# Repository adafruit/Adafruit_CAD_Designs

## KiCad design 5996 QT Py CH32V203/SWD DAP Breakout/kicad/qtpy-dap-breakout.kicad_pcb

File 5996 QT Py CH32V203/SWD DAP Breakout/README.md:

# QT Py CH32V203 SWD DAP Breakout

A 40 x 42 mm carrier that turns an Adafruit QT Py CH32V203 into a debug probe. The silk title is "WCH + ARM Programmer". It works two ways:

| Mode | Targets |
|---|---|
| WCH SWIO programmer | Metro CH32V407 and CH32V467 |
| ARM SWD CMSIS-DAP probe | ARM Cortex targets on the 10-pin header |

No pull-up resistor is needed on SWIO. The SWIO firmware is in [Adafruit_DAP PR #60](https://github.com/adafruit/Adafruit_DAP/pull/60).

The QT Py plugs into the inner rows of two 2x7 SMD sockets. The outer rows repeat every QT Py pin, so you can plug jumper wires in for the spare IO, like the Proto Doubler PiCowbell. A 2x5 1.27 mm box header takes a 1675 cable to the target. It is a single-sided board made to be cut at home on a laser or a mill: no vias, a GND pour, 45 degree bends only.

## Files

| File | What |
|---|---|
| [5996 QT Py CH32V203 SWD DAP Breakout.stpZ](5996%20QT%20Py%20CH32V203%20SWD%20DAP%20Breakout.stpZ) | Board with QT Py, sockets and box header, gzipped STEP |
| [kicad/qtpy-dap-breakout.kicad_pcb](kicad/qtpy-dap-breakout.kicad_pcb) | KiCad 10 board |
| [kicad/qtpy-dap-breakout.kicad_pro](kicad/qtpy-dap-breakout.kicad_pro) | KiCad 10 project |
| [kicad/build_pcb.py](kicad/build_pcb.py) | Regenerates the board from scratch |
| [kicad/fp-lib-table](kicad/fp-lib-table) | Points KiCad at `models/QTPyDAP.pretty` |
| [models/QTPyDAP.pretty](models/QTPyDAP.pretty) | 752 box header footprint |
| [models/BoxHeader_2x05_P1.27mm_SMD_752.step](models/BoxHeader_2x05_P1.27mm_SMD_752.step) | 752 box header STEP |
| [models/QTPy_CH32V203_5996.stpZ](models/QTPy_CH32V203_5996.stpZ) | QT Py CH32V203 model, gzipped STEP |
| [models/gen_box_header_752.py](models/gen_box_header_752.py) | Generates the box header model |
| [milling/qtpy-dap-breakout-F_Cu.gbr](milling/qtpy-dap-breakout-F_Cu.gbr) | F.Cu Gerber |
| [milling/qtpy-dap-breakout-Edge_Cuts.gbr](milling/qtpy-dap-breakout-Edge_Cuts.gbr) | Edge.Cuts Gerber |
| [milling/qtpy-dap-breakout.drl](milling/qtpy-dap-breakout.drl) | Drill file |
| [milling/qtpy-dap-breakout-job.gbrjob](milling/qtpy-dap-breakout-job.gbrjob) | Gerber job file |
| [milling/F_Cu-reference.pdf](milling/F_Cu-reference.pdf) | 1:1 etch PDF |
| [milling/F_Cu-mirrored-1to1.pdf](milling/F_Cu-mirrored-1to1.pdf) | 1:1 etch PDF, mirrored |

A SKADIS mount for this board, with its STEP, 3MF and FreeCAD files, is in [SKADIS Mount](../SWD%20DAP%20Breakout%20SKADIS%20Mount).

## Parts

| Ref | Part | Qty |
|---|---|---|
| U1 | Adafruit QT Py CH32V203 (PID 5996) | 1 |
| J1, J2 | 2x7 2.54 mm SMD female socket, cut from an Adafruit 2187 2x20 short SMT socket, one per QT Py side | 2 |
| J3 | Adafruit 752 2x5 1.27 mm SMT box header, 10-pin ARM Cortex | 1 |
| J4, J5 | 1x7 2.54 mm male header strip, solders to the QT Py | 2 |
| | Adafruit 1675 SWD cable, 2x5 1.27 mm, 150 mm | 1 |
| | M2 x 4 screw, into the SKADIS mount's heat set inserts | 4 |
| | Single-sided copper-clad blank, 40 x 42 mm | 1 |

## Pinout

| Header J3 | Signal | QT Py | Metro CH32V407/467 (JDEBUG) |
|---|---|---|---|
| 1 | VTref | not connected | 1, the Metro's own 3.3 V |
| 2 | SWDIO / SWIO | A3 | 2 (PA13) |
| 3, 5, 9 | GND | GND | 3, 5, 9 |
| 4 | SWCLK | A2 | 4 (PA14, unused in SWIO mode) |
| 6, 7, 8 | not connected | | |
| 10 | nRESET | A0 | 10 |

- Only 3.3 V targets. There is no level shifting.
- The breakout does not power the target, like the Raspberry Pi Debug Probe. The target needs its own supply. Pin 1 is left open so the Metro's 3.3 V never meets the QT Py's.
- The UART is not wired to the box header. TX and RX, like every other QT Py pin, are on the outer socket rows.
- Each QT Py pin has a second socket on the outer row, labeled on the silk. The two contacts of each pin are tied by a trace under the socket.

## Firmware

Liz Clark's Adafruit_DAP examples run as-is with this wiring.

| Example | Result |
|---|---|
| `ch32_host/cmsis_dap_probe` | Runs as-is. Its UART bridge is on the QT Py TX and RX pins, reachable on the outer socket rows |
| `ch32_host/dragdrop_programmer` | Runs as-is |
| `stm32/stm32f4_test` | Runs as-is |

Most other examples do not fit this board:

| Group | Examples | Why |
|---|---|---|
| Needs pin changes | `samd21/flash_MKR_bootloaders`, `samd51/samx5_flash_from_header`, `nrf/nrf52_test` | Pins are hardcoded. The samx5 image may not fit in flash |
| Needs SD card, SPI flash or WiFi | `samd21/flash_from_SD`, `samd21/flash_from_SPI_flash`, `samd21/SWD_standalone_core`, `stm32/stm32_flash_from_SD`, `nrf/flash_feather52`, `nrf/flash_feather52840`, `nrf/flash_nrf51_from_SPI_flash`, `ESPHost/*` | The breakout has none of these |
| Image too large | `samd21/flash_from_header` | 239 KB image, more than 7 times the 32 KB flash |

Tested through the breakout:

| Target | Firmware | Result |
|---|---|---|
| Metro CH32V407 | [Adafruit_DAP PR #60](https://github.com/adafruit/Adafruit_DAP/pull/60) | Programmed and verified in 66.5 s |
| Metro CH32V467 | [Adafruit_DAP PR #60](https://github.com/adafruit/Adafruit_DAP/pull/60) | Programmed and verified TinyUF2 in 67.0 s, chip ID 10/10 |
| Metro M0 Express (SAMD21G18A) | `ch32_host/cmsis_dap_probe` | Read over SWD with OpenOCD at 400 kHz |

## Milling

Cut on F.Cu only. Signal traces are 0.76 mm with 45 degree miters. GND is a pour with 0.5 mm clearance and solid pad connections, with no GND traces. The tightest gap is 0.51 mm between the box header pads. A fiber laser such as the xTool F1 Ultra handles it; a mill needs a 0.4 mm end mill or a fine V-bit.

The Metro and QT Py in the renders are approximate models, not official CAD.

In the Data 70 font, D reads like O ("SWD", "GND") and 1 reads like I in the date.

## Credits

Probe firmware by Liz Clark (Adafruit_DAP, ch32_host examples). The QT Py model is built from Liz's [QT Py CH32V203 Eagle board](https://github.com/adafruit/Adafruit-QT-Py-CH32V203-PCB).

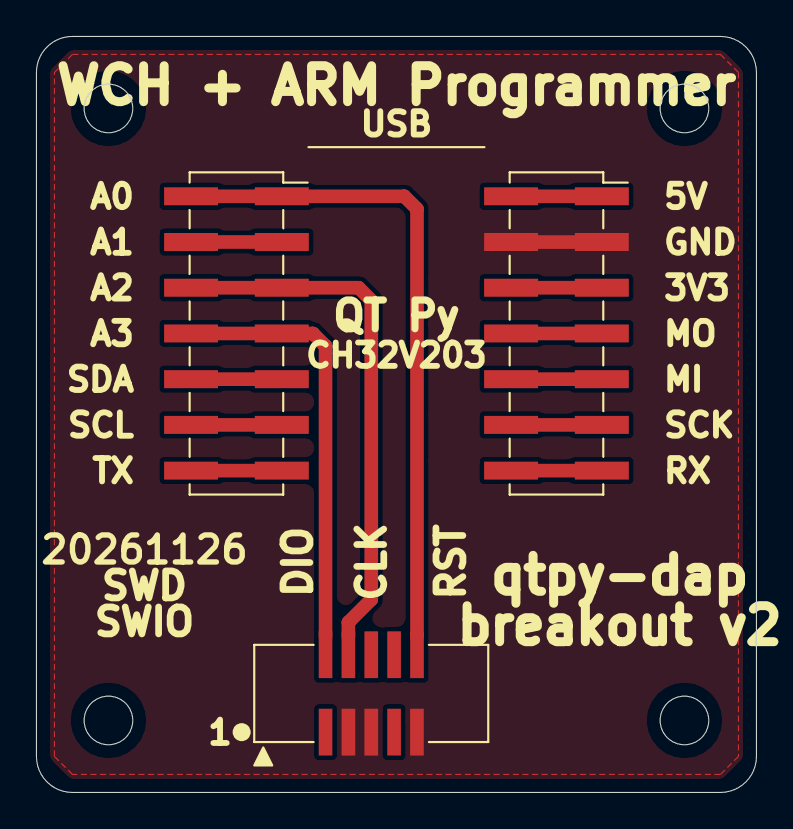
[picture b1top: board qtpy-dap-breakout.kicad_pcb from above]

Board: 2 copper layers, 40.0 x 42.0 mm, 4 parts (0 on the bottom side), 14 nets.

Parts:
J1: QT Py left (2187 cut 2x7); PinSocket_2x07_P2.54mm_Vertical_SMD
J2: QT Py right (2187 cut 2x7); PinSocket_2x07_P2.54mm_Vertical_SMD
J3: SWD 2x5 (752); BoxHeader_2x05_P1.27mm_SMD_752
U1: QT Py CH32V203 (5996)

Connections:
3V3: J2.5, J2.6
5V: J2.1, J2.2
A1: J1.3, J1.4
GND: J2.3, J2.4, J3.3, J3.5, J3.9
MI: J2.9, J2.10
MO: J2.7, J2.8
RST: J1.1, J1.2, J3.10
RX: J2.13, J2.14
SCK: J2.11, J2.12
SCL: J1.11, J1.12
SDA: J1.9, J1.10
SWCLK: J1.5, J1.6, J3.4
SWDIO: J1.7, J1.8, J3.2
TX: J1.13, J1.14
